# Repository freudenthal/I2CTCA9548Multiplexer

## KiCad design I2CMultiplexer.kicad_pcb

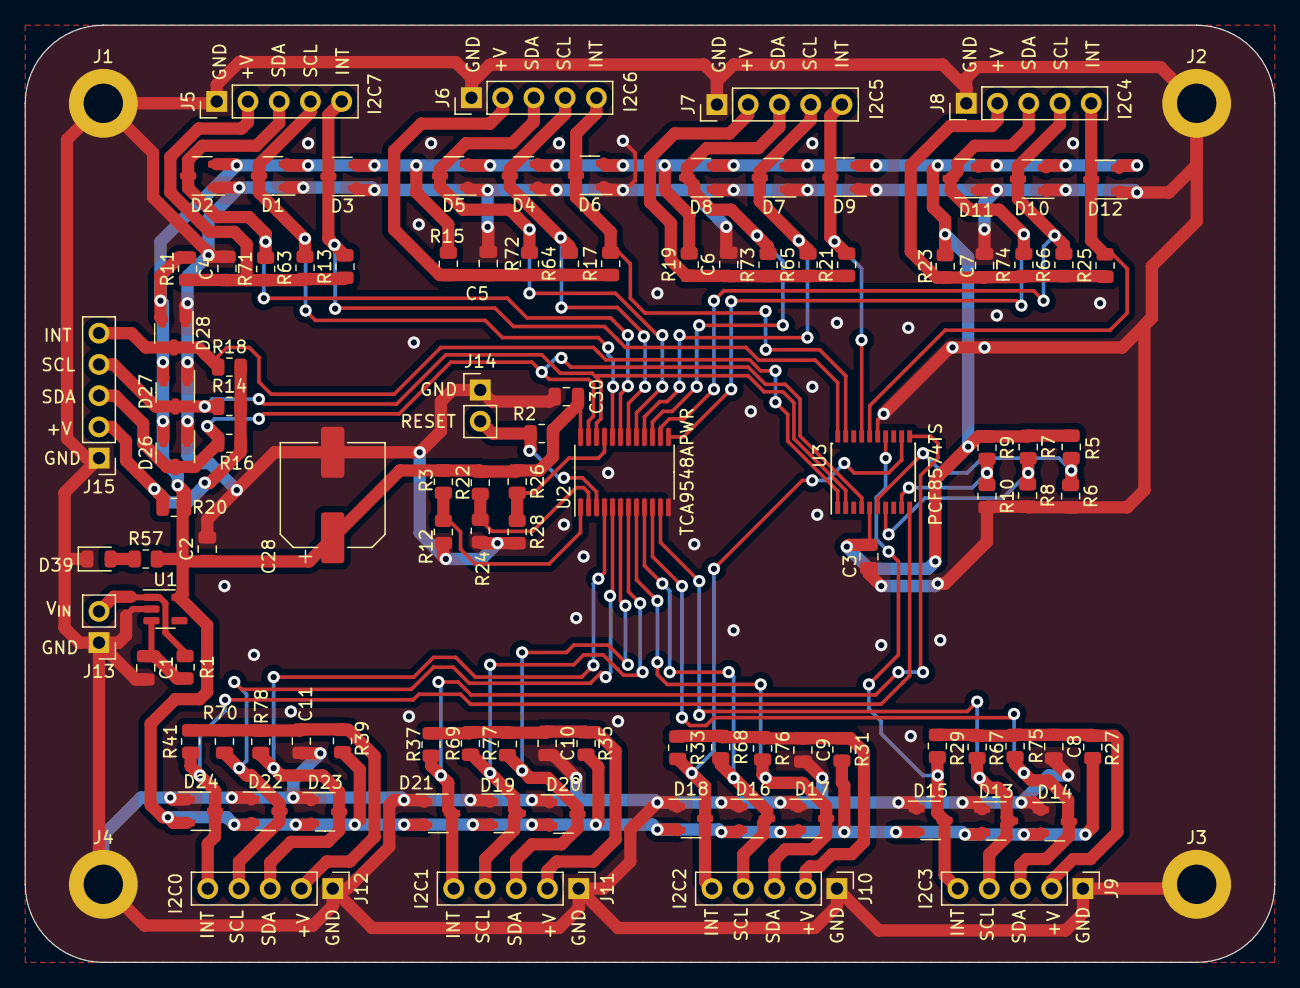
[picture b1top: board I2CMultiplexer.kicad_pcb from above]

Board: 2 copper layers, 101.6 x 76.2 mm, 110 parts (0 on the bottom side), 48 nets.

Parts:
C1, C2, C3, C4, C5, C6, C7, C8, C9, C10, C11, C30: 1uF; C_0805_2012Metric
C28: 100uF; CP_Elec_8x11.9
D1, D2, D3, D4, D5, D6, D7, D8, D9, D10, D11, D12, D13, D14, D15, D16, D17, D18, D19, D20, D21, D22, D23, D24, D26, D27, D28: 100V; SOT-23-3
D39: LED; LED_0805_2012Metric
J1, J2, J3, J4: M3; MountingHole_3.2mm_M3_DIN965_Pad
J5, J6, J7, J8, J9, J10, J11, J12, J15: I2C; PinHeader_1x05_P2.54mm_Vertical
J13: V_{IN}; PinHeader_1x02_P2.54mm_Vertical
J14: ~{RESET}; PinHeader_1x02_P2.54mm_Vertical
R1: 100kΩ; R_0805_2012Metric
R2, R3, R5, R6, R7, R8, R9, R10, R12, R13, R14, R16, R17, R18, R21, R22, R24, R25, R26, R28, R29, R33, R37, R41, R63, R64, R65, R66, R67, R68, R69, R70, R71, R72, R73, R74, R75, R76, R77, R78: 10kΩ; R_0805_2012Metric
R11, R15, R19, R23, R27, R31, R35, R39: 0Ω; R_0805_2012Metric
R20: NS; R_0805_2012Metric
R57: 500Ω; R_0805_2012Metric
U1: MAX40200AUK; SOT-23-5
U2: TCA9548APWR; TSSOP-24_4.4x7.8mm_P0.65mm
U3: PCF8574TS; SSOP-20_4.4x6.5mm_P0.65mm

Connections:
+5V: C2.1, C3.1, C28.1, C30.1, D1.2 (K), D2.2 (K), D3.2 (K), D4.2 (K), D5.2 (K), D6.2 (K), D7.2 (K), D8.2 (K), D9.2 (K), D10.2 (K), D11.2 (K), D12.2 (K), D13.2 (K), D14.2 (K), D15.2 (K), D16.2 (K), D17.2 (K), D18.2 (K), D19.2 (K), D20.2 (K), D21.2 (K), D22.2 (K), D23.2 (K), D24.2 (K), D26.2 (K), D27.2 (K), D28.2 (K), R2.1, R3.1, R5.1, R7.1, R9.1, R11.2, R15.2, R19.2, R20.2, R22.1, R23.2, R26.1, R27.2, R31.2, R35.2, R39.2, R57.2, U1.5 (OUT), U2.24 (VCC), U3.5 (VDD)
/I2CInput/INT: D28.3 (A), J15.5, R18.1, U3.1 (~INT)
/I2CInput/SCL: D27.3 (A), J15.4, R14.1, U2.22 (SCL), U3.2 (SCL)
/I2CInput/SDA: D26.3 (A), J15.3, R16.1, U2.23 (SDA), U3.4 (SDA)
/I2CInput/VI2C: J15.2, R14.2, R16.2, R18.2, R20.1
/TCA9548AI2CMultiplexer/A0: R3.2, R12.1, U2.1 (A0)
/TCA9548AI2CMultiplexer/A1: R22.2, R24.1, U2.2 (A1)
/TCA9548AI2CMultiplexer/A2: R26.2, R28.1, U2.21 (A2)
/TCA9548AI2CMultiplexer/I2CConnector1/INT: D6.3 (A), J6.5, R17.2, U3.19 (P6)
/TCA9548AI2CMultiplexer/I2CConnector1/SCL: D4.3 (A), J6.4, R64.2, U2.18 (SC6)
/TCA9548AI2CMultiplexer/I2CConnector1/SDA: D5.3 (A), J6.3, R72.2, U2.17 (SD6)
/TCA9548AI2CMultiplexer/I2CConnector1/VBus: C5.1, J6.2, R15.1, R17.1, R64.1, R72.1
/TCA9548AI2CMultiplexer/I2CConnector2/INT: D9.3 (A), J7.5, R21.2, U3.17 (P5)
/TCA9548AI2CMultiplexer/I2CConnector2/SCL: D7.3 (A), J7.4, R65.2, U2.16 (SC5)
/TCA9548AI2CMultiplexer/I2CConnector2/SDA: D8.3 (A), J7.3, R73.2, U2.15 (SD5)
/TCA9548AI2CMultiplexer/I2CConnector2/VBus: C6.1, J7.2, R19.1, R21.1, R65.1, R73.1
/TCA9548AI2CMultiplexer/I2CConnector3/INT: D12.3 (A), J8.5, R25.2, U3.16 (P4)
/TCA9548AI2CMultiplexer/I2CConnector3/SCL: D10.3 (A), J8.4, R66.2, U2.14 (SC4)
/TCA9548AI2CMultiplexer/I2CConnector3/SDA: D11.3 (A), J8.3, R74.2, U2.13 (SD4)
/TCA9548AI2CMultiplexer/I2CConnector3/VBus: C7.1, J8.2, R23.1, R25.1, R66.1, R74.1
/TCA9548AI2CMultiplexer/I2CConnector4/INT: D15.3 (A), J9.5, R29.2, U3.14 (P3)
/TCA9548AI2CMultiplexer/I2CConnector4/SCL: D13.3 (A), J9.4, R67.2, U2.11 (SC3)
/TCA9548AI2CMultiplexer/I2CConnector4/SDA: D14.3 (A), J9.3, R75.2, U2.10 (SD3)
/TCA9548AI2CMultiplexer/I2CConnector4/VBus: C8.1, J9.2, R27.1, R29.1, R67.1, R75.1
/TCA9548AI2CMultiplexer/I2CConnector5/INT: D18.3 (A), J10.5, R33.2, U3.12 (P2)
/TCA9548AI2CMultiplexer/I2CConnector5/SCL: D16.3 (A), J10.4, R68.2, U2.9 (SC2)
/TCA9548AI2CMultiplexer/I2CConnector5/SDA: D17.3 (A), J10.3, R76.2, U2.8 (SD2)
/TCA9548AI2CMultiplexer/I2CConnector5/VBus: C9.1, J10.2, R31.1, R33.1, R68.1, R76.1
/TCA9548AI2CMultiplexer/I2CConnector6/INT: D21.3 (A), J11.5, R37.2, U3.11 (P1)
/TCA9548AI2CMultiplexer/I2CConnector6/SCL: D19.3 (A), J11.4, R69.2, U2.7 (SC1)
/TCA9548AI2CMultiplexer/I2CConnector6/SDA: D20.3 (A), J11.3, R77.2, U2.6 (SD1)
/TCA9548AI2CMultiplexer/I2CConnector6/VBus: C10.1, J11.2, R35.1, R37.1, R69.1, R77.1
/TCA9548AI2CMultiplexer/I2CConnector7/INT: D24.3 (A), J12.5, R41.2, U3.10 (P0)
/TCA9548AI2CMultiplexer/I2CConnector7/SCL: D22.3 (A), J12.4, R70.2, U2.5 (SC0)
/TCA9548AI2CMultiplexer/I2CConnector7/SDA: D23.3 (A), J12.3, R78.2, U2.4 (SD0)
/TCA9548AI2CMultiplexer/I2CConnector7/VBus: C11.1, J12.2, R39.1, R41.1, R70.1, R78.1
/TCA9548AI2CMultiplexer/I2CConnector/INT: D3.3 (A), J5.5, R13.2, U3.20 (P7)
/TCA9548AI2CMultiplexer/I2CConnector/SCL: D1.3 (A), J5.4, R63.2, U2.20 (SC7)
/TCA9548AI2CMultiplexer/I2CConnector/SDA: D2.3 (A), J5.3, R71.2, U2.19 (SD7)
/TCA9548AI2CMultiplexer/I2CConnector/VBus: C4.1, J5.2, R11.1, R13.1, R63.1, R71.1
GND: C1.2, C2.2, C3.2, C4.2, C5.2, C6.2, C7.2, C8.2, C9.2, C10.2, C11.2, C28.2, C30.2, D1.1 (K), D2.1 (K), D3.1 (K), D4.1 (K), D5.1 (K), D6.1 (K), D7.1 (K), D8.1 (K), D9.1 (K), D10.1 (K), D11.1 (K), D12.1 (K), D13.1 (K), D14.1 (K), D15.1 (K), D16.1 (K), D17.1 (K), D18.1 (K), D19.1 (K), D20.1 (K), D21.1 (K), D22.1 (K), D23.1 (K), D24.1 (K), D26.1 (K), D27.1 (K), D28.1 (K), D39.1 (K), J1.1, J2.1, J3.1, J4.1, J5.1, J6.1, J7.1, J8.1, J9.1, J10.1, J11.1, J12.1, J13.1, J14.1, J15.1, R6.2, R8.2, R10.2, R12.2, R24.2, R28.2, U1.2 (GND), U2.12 (GND), U3.15 (VSS)
unnamed: D39.2 (A), R57.1
unnamed: J13.2, R1.2, U1.1 (VDD)
unnamed: J14.2, R2.2, U2.3 (~RESET)
unnamed: C1.1, R1.1, U1.3 (EN)
unnamed: R5.2, R6.1, U3.6 (A0)
unnamed: R7.2, R8.1, U3.7 (A1)
unnamed: R9.2, R10.1, U3.9 (A2)

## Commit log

2024-01-01 Initial commit.
2024-01-02 Start layout. Swap side for connectors.
2024-01-03 Swap I2C connections.
2024-01-08 Added labels. Ready for final cleanup and checking.
